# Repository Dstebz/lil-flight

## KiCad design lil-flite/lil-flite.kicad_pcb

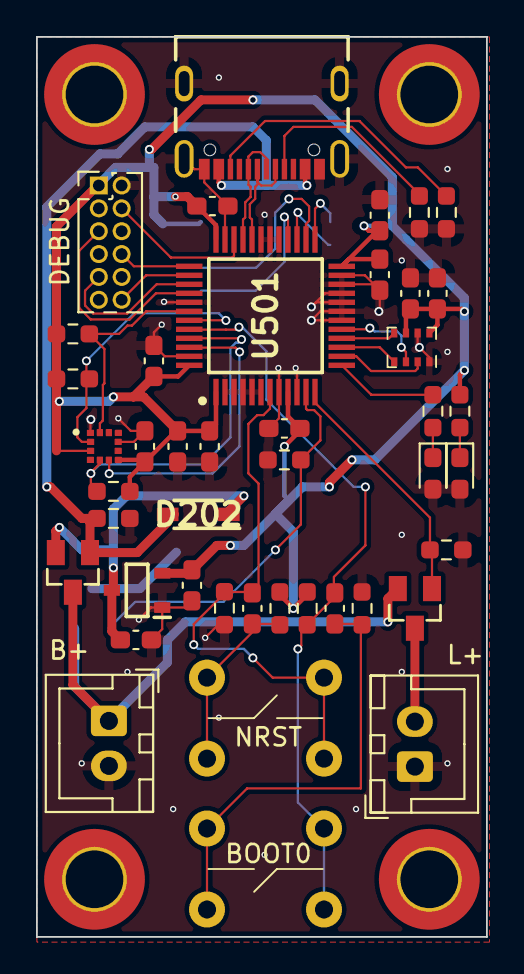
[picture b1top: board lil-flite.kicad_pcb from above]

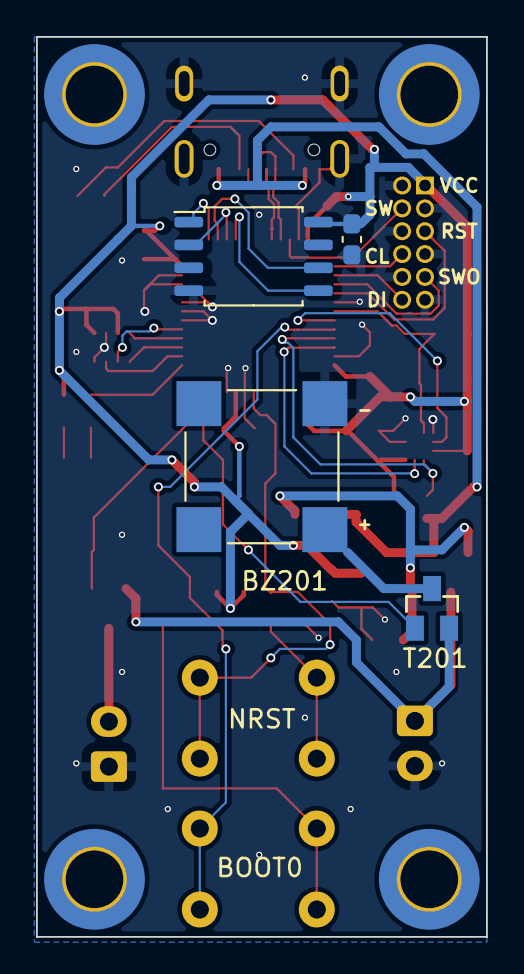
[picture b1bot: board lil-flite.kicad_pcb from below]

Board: 4 copper layers, 25.0 x 50.0 mm, 51 parts (4 on the bottom side), 37 nets.

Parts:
BZ201: CMT-8504-100-SMT-TR; XDCR_CMT-8504-100-SMT-TR
C201, C202, C407: 1uF; C_0603_1608Metric_Pad1.08x0.95mm_HandSolder
C301, C302, C303, C401, C402, C403, C404, C405, C406, C409, C410: 100nF; C_0603_1608Metric_Pad1.08x0.95mm_HandSolder
C408: 10uF; C_0603_1608Metric_Pad1.08x0.95mm_HandSolder
D201: RED LED; LED_0603_1608Metric_Pad1.05x0.95mm_HandSolder
D202: 1N4148W-7-F; SOD3716X145N
D501: BLUE LED; LED_0603_1608Metric_Pad1.05x0.95mm_HandSolder
H201, H202, H203, H204: MountingHole; MountingHole_3.2mm_M3_DIN965_Pad_TopBottom
J201: USB4105-GF-A; GCT_USB4105-GF-A
J202, J203: Conn_01x02; JST_XH_B2B-XH-A_1x02_P2.50mm_Vertical
J204: Conn_02x06_Odd_Even; PinHeader_2x06_P1.27mm_Vertical
PS201: XC6206P332MR-G; SOT95P280X130-3N
R201, R407: 330R; R_0603_1608Metric_Pad0.98x0.95mm_HandSolder
R202, R203, R405, R406: 10k; R_0603_1608Metric_Pad0.98x0.95mm_HandSolder
R204, R401, R402: 1k; R_0603_1608Metric_Pad0.98x0.95mm_HandSolder
R205, R206: 5k1; R_0603_1608Metric_Pad0.98x0.95mm_HandSolder
R301, R302, R303: 4k7; R_0603_1608Metric_Pad0.98x0.95mm_HandSolder
SW401, SW402: PTS645SM70-2 LFS
T201, T202, T203: AO3401A; SOT23-3L
U301: BMP280; Bosch_LGA-8_2x2.5mm_P0.65mm_ClockwisePinNumbering
U302: MC6470; PQFN50P200X200X100-12N
U401: W25Q128JVSIQ; SOIC-8_5.23x5.23mm_P1.27mm
U501: STM32F103C8T6; QFP50P900X900X160-48N

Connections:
+5V: D202.2 (A), J201.A4_B9 (VBUS), J201.B4_A9 (VBUS), R204.1 (+), T202.1
+BATT: J202.1, T201.2, T202.3, T203.2
/Connectors + Power/JTAG.CLK: J204.8, U501.37 (PA14)
/Connectors + Power/JTAG.DI: J204.12, U501.38 (PA15)
/Connectors + Power/JTAG.DOSWO: J204.9, U501.39 (PB3)
/Connectors + Power/JTAG.MSSWDIO: J204.4, U501.34 (PA13)
/Connectors + Power/JTAG.NJTRST: J204.5, U501.40 (PB4)
/Connectors + Power/MISC.Buzzer_PWM: R202.2 (-), T201.1, U501.11 (PA1)
/Connectors + Power/MISC.RECOVERY_LED_PWM: R203.2 (-), T203.1, U501.12 (PA2)
/Connectors + Power/RECOVERY_LED: J203.2, T203.3
/Connectors + Power/USB.CC1: J201.A5 (CC1), R205.2 (-)
/Connectors + Power/USB.CC2: J201.B5 (CC2), R206.2 (-)
/Connectors + Power/USB.Data_+: J201.A6 (DP1), J201.B6 (DP2), U501.33 (PA12)
/Connectors + Power/USB.Data_-: J201.A7 (DN1), J201.B7 (DN2), U501.32 (PA11)
/MCU/BMP.MISO: U301.5 (SDO), U501.16 (PA6)
/MCU/BMP.MOSI: U301.3 (SDI), U501.17 (PA7)
/MCU/BMP.NSS: U301.2 (CSB), U501.14 (PA4)
/MCU/BMP.SCK: U301.4 (SCK), U501.15 (PA5)
/MCU/FLASH.MISO: U401.2 (DO(IO1)), U501.27 (PB14)
/MCU/FLASH.MOSI: U401.5 (DI(IO0)), U501.28 (PB15)
/MCU/FLASH.NSS: U401.1 (~CS), U501.25 (PB12)
/MCU/FLASH.SCK: U401.6 (CLK), U501.26 (PB13)
/MCU/IMU.INTA: R303.1 (+), U302.5 (INTA), U501.45 (PB8)
/MCU/IMU.INTM: U302.6 (INTM), U501.46 (PB9)
/MCU/IMU.SCL: R302.1 (+), U302.12 (SCL), U501.42 (PB6)
/MCU/IMU.SDA: R301.1 (+), U302.2 (SDA), U501.43 (PB7)
/MCU/MCU_BOOT0: C409.2 (-), R405.2 (-), SW402.1, SW402.3, U501.44 (BOOT0)
/MCU/MCU_GPLED: R407.2 (-), U501.13 (PA3)
/MCU/MCU_NRST: C406.1 (+), R406.1 (+), SW401.2, SW401.4, U501.7 (NRST)
GND: BZ201.N (+), C201.1 (+), C202.1 (+), C301.1 (+), C302.1 (+), C303.1 (+), C401.1 (+), C402.1 (+), C403.1 (+), C404.1 (+), C405.1 (+), C407.1 (+), C408.1 (+), C410.1 (+), D201.2 (A), D501.2 (A), J201.A1_B12 (GND), J201.B1_A12 (GND), J201.S1 (SHELL_GND), J201.S2 (SHELL_GND), J201.S3 (SHELL_GND), J201.S4 (SHELL_GND), J202.2, J203.1, J204.2, J204.3, J204.6, J204.7, J204.10, J204.11, PS201.1 (VSS), R202.1 (+), R203.1 (+), R204.2 (-), R205.1 (+), R206.1 (+), R402.2 (-), R406.2 (-), U301.1 (GND), U301.7 (GND), U302.1 (A5), U302.9 (GND), U401.4 (GND), U501.2 (PC13-TAMPER-RTC), U501.3 (PC14-OSC32_IN), U501.4 (PC15-OSC32_OUT), U501.5 (PD0_OSC_IN), U501.6 (PD1_OSC_OUT), U501.8 (VSSA), U501.10 (PA0_WKUP), U501.18 (PB0), U501.19 (PB1), U501.20 (PB2), U501.21 (PB10), U501.22 (PB11), U501.23 (VSS), U501.29 (PA8), U501.30 (PA9), U501.31 (PA10), U501.35 (VSS), U501.41 (PB5), U501.47 (VSS)
unnamed: BZ201.P (-), T201.3
unnamed: C202.2 (-), D202.1 (K), PS201.3 (VIN), T202.2
unnamed: C406.2 (-), R401.2 (-), SW401.1, SW401.3
unnamed: C409.1 (+), R402.1 (+), SW402.2, SW402.4
unnamed: D201.1 (K), R201.1 (+)
unnamed: D501.1 (K), R407.1 (+)
VCC: C201.2 (-), C301.2 (-), C302.2 (-), C303.2 (-), C401.2 (-), C402.2 (-), C403.2 (-), C404.2 (-), C405.2 (-), C407.2 (-), C408.2 (-), C410.2 (-), J204.1, PS201.2 (VOUT), R201.2 (-), R301.2 (-), R302.2 (-), R303.2 (-), R401.1 (+), R405.1 (+), U301.6 (VDDIO), U301.8 (VDD), U302.3 (VDDIO), U302.7 (VDDM), U401.8 (VCC), U501.1 (VBAT), U501.9 (VDDA), U501.24 (VDD), U501.36 (VDD), U501.48 (VDD)

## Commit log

2023-08-12 Initial Commit
    Added a load of things
2023-08-12 aaa
    adding buttons
    changin layout
2023-08-13 Almost finished
    Need to double check everything
    routing done
    more vias maybe
